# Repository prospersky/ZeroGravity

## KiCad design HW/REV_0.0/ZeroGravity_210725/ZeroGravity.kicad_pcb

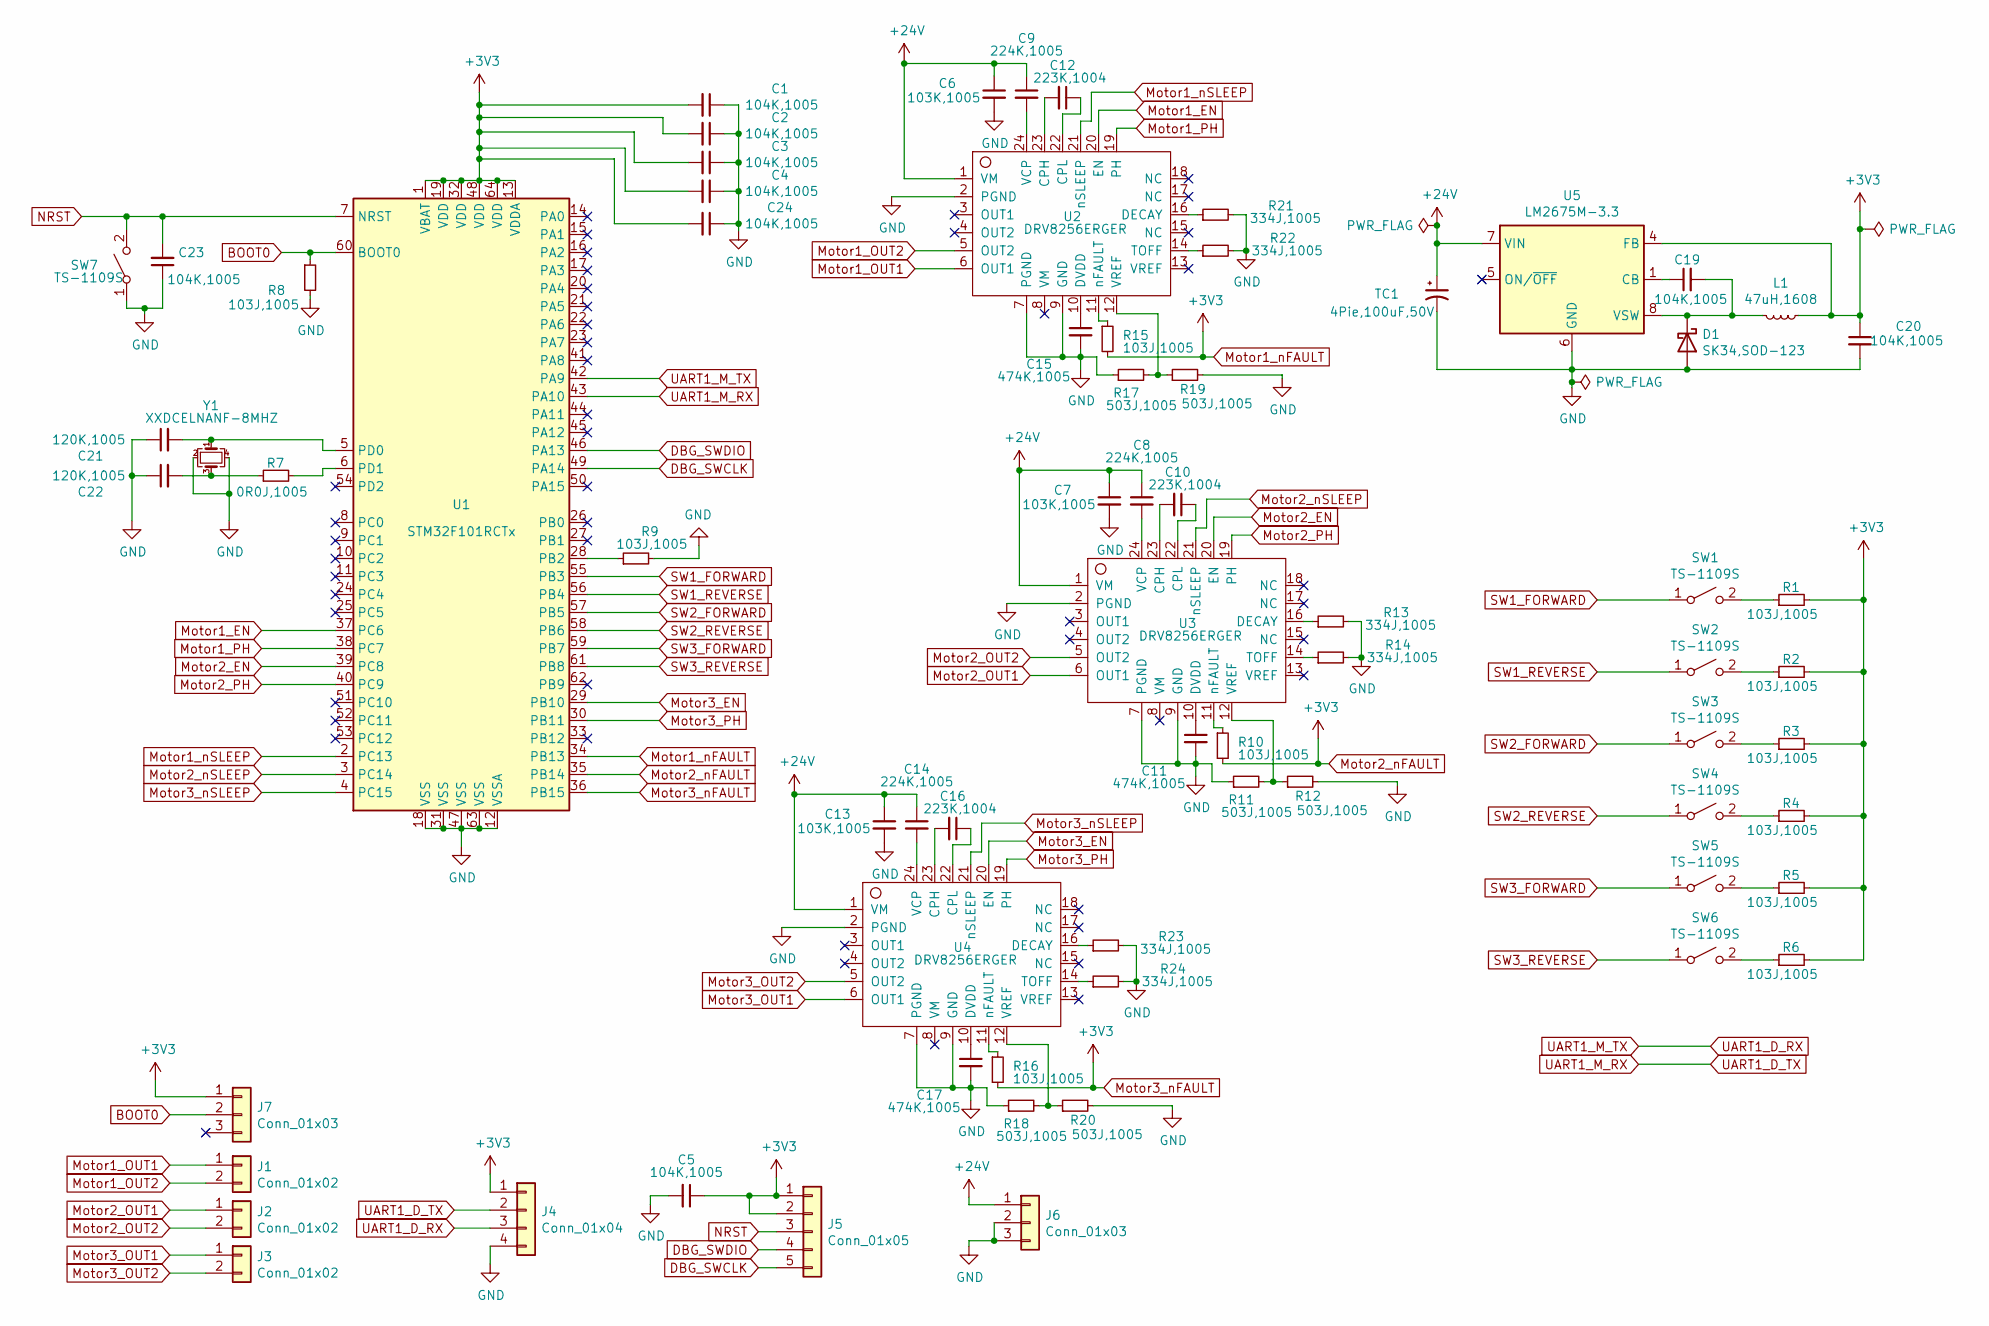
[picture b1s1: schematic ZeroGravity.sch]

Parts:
C1, C2, C3, C4, C5, C19, C20, C23, C24: 104K,1005; C_0402_1005Metric
C6, C7, C13: 103K,1005; C_0402_1005Metric
C8, C9, C14: 224K,1005; C_0402_1005Metric
C10, C12, C16: 223K,1004; C_0402_1005Metric
C11, C15, C17: 474K,1005; C_0402_1005Metric
C21, C22: 120K,1005; C_0402_1005Metric
D1: SK34,SOD-123; D_SOD-123F
J1, J2, J3: Conn_01x02; Molex_PicoBlade_53047-0210_1x02_P1.25mm_Vertical
J4: Conn_01x04; Molex_PicoBlade_53047-0410_1x04_P1.25mm_Vertical
J5: Conn_01x05; Molex_PicoBlade_53047-0510_1x05_P1.25mm_Vertical
J6, J7: Conn_01x03; Molex_PicoBlade_53047-0310_1x03_P1.25mm_Vertical
L1: 47uH,1608; L_0603_1608Metric
R1, R2, R3, R4, R5, R6, R8, R9, R10, R15, R16: 103J,1005; R_0402_1005Metric
R7: 0R0J,1005; R_0402_1005Metric
R11, R12, R17, R18, R19, R20: 503J,1005; R_0402_1005Metric
R13, R14, R21, R22, R23, R24: 334J,1005; R_0402_1005Metric
SW1, SW2, SW3, SW4, SW5, SW6, SW7: TS-1109S; Switch_Tactile_TS-1109S
TC1: 4Pie,100uF,50V; CP_Elec_8x10.5
U1: STM32F101RCTx; LQFP-64_10x10mm_P0.5mm
U2, U3, U4: DRV8256ERGER; VQFN-24-1EP_4x4mm_P0.5mm_EP2.45x2.45mm_ThermalVias
U5: LM2675M-3.3; SOIC-8_3.9x4.9mm_P1.27mm
Y1: XXDCELNANF-8MHZ; Crystal_SMD_7050-4Pin_7.0x5.0mm

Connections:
+24V: C6.1, C7.1, C8.1, C9.1, C13.1, C14.1, J6.1, TC1.1, U2.1 (VM), U3.1 (VM), U4.1 (VM), U5.7 (VIN)
BOOT0: J7.2, R8.1, U1.60 (BOOT0); also elsewhere on the board
DBG_SWCLK: J5.5, U1.49 (PA14)
DBG_SWDIO: J5.4, U1.46 (PA13)
GND: C1.1, C2.1, C3.1, C4.1, C5.2, C6.2, C7.2, C11.2, C13.2, C15.2, C17.2, C20.2, C21.1, C22.1, C23.1, C24.1, D1.2 (A), J4.4, J6.2, J6.3, R8.2, R9.2, R11.1, R12.2, R13.2, R14.2, R17.1, R18.1, R19.2, R20.2, R21.2, R22.2, R23.2, R24.2, SW7.1 (A), TC1.2, U1.12 (VSSA), U1.18 (VSS), U1.31 (VSS), U1.47 (VSS), U1.63 (VSS), U2.2 (PGND), U2.7 (PGND), U2.9 (GND), U3.2 (PGND), U3.7 (PGND), U3.9 (GND), U4.2 (PGND), U4.7 (PGND), U4.9 (GND), U5.6 (GND), Y1.2, Y1.4
Motor1_EN: U1.37 (PC6), U2.20 (EN)
Motor1_OUT1: J1.1, U2.6 (OUT1)
Motor1_OUT2: J1.2, U2.5 (OUT2)
Motor1_PH: U1.38 (PC7), U2.19 (PH)
Motor1_nFAULT: C1.2, C2.2, C3.2, C4.2, C5.1, C20.1, C24.2, J4.1, J5.1, J5.2, J7.1, L1.1, R1.2, R2.2, R3.2, R4.2, R5.2, R6.2, R10.2, R15.2, R16.2, U1.1 (VBAT), U1.13 (VDDA), U1.19 (VDD), U1.32 (VDD), U1.34 (PB13), U1.35 (PB14), U1.36 (PB15), U1.48 (VDD), U1.64 (VDD), U5.4 (FB)
Motor1_nSLEEP: U1.2 (PC13), U2.21 (nSLEEP)
Motor2_EN: U1.39 (PC8), U3.20 (EN)
Motor2_OUT1: J2.1, U3.6 (OUT1)
Motor2_OUT2: J2.2, U3.5 (OUT2)
Motor2_PH: U1.40 (PC9), U3.19 (PH)
Motor2_nSLEEP: U1.3 (PC14), U3.21 (nSLEEP)
Motor3_EN: U1.29 (PB10), U4.20 (EN)
Motor3_OUT1: J3.1, U4.6 (OUT1)
Motor3_OUT2: J3.2, U4.5 (OUT2)
Motor3_PH: U1.30 (PB11), U4.19 (PH)
Motor3_nSLEEP: U1.4 (PC15), U4.21 (nSLEEP)
NRST: C23.2, J5.3, SW7.2 (B), U1.7 (NRST)
unnamed: C8.2, U3.24 (VCP)
unnamed: C9.2, U2.24 (VCP)
unnamed: C10.1, U3.22 (CPL)
unnamed: C10.2, U3.23 (CPH)
unnamed: C11.1, U3.10 (DVDD)
unnamed: C12.1, U2.22 (CPL)
unnamed: C12.2, U2.23 (CPH)
unnamed: C14.2, U4.24 (VCP)
unnamed: C15.1, U2.10 (DVDD)
unnamed: C16.1, U4.22 (CPL)
unnamed: C16.2, U4.23 (CPH)
unnamed: C17.1, U4.10 (DVDD)
unnamed: C19.1, U5.1 (CB)
unnamed 35: C19.2, D1.1 (K), L1.2, U5.8 (VSW); also elsewhere on the board
unnamed: C21.2, U1.5 (PD0), Y1.1
unnamed: C22.2, R7.1, Y1.3
unnamed: R1.1, SW1.2 (B)
unnamed: R2.1, SW2.2 (B)
unnamed: R3.1, SW3.2 (B)
unnamed: R4.1, SW4.2 (B)
unnamed: R5.1, SW5.2 (B)
unnamed: R6.1, SW6.2 (B)
unnamed: R7.2, U1.6 (PD1)
unnamed: R9.1, U1.28 (PB2)
unnamed: R10.1, U3.11 (nFAULT)
unnamed: R11.2, R12.1, U3.12 (VREF)
unnamed: R13.1, U3.16 (DECAY)
unnamed: R14.1, U3.14 (TOFF)
unnamed: R15.1, U2.11 (nFAULT)
unnamed: R16.1, U4.11 (nFAULT)
unnamed: R17.2, R19.1, U2.12 (VREF)
unnamed: R18.2, R20.1, U4.12 (VREF)
unnamed: R21.1, U2.16 (DECAY)
unnamed: R22.1, U2.14 (TOFF)
unnamed: R23.1, U4.16 (DECAY)
unnamed: R24.1, U4.14 (TOFF)
SW1_FORWARD: SW1.1 (A), U1.55 (PB3)
SW1_REVERSE: SW2.1 (A), U1.56 (PB4)
SW2_FORWARD: SW3.1 (A), U1.57 (PB5)
SW2_REVERSE: SW4.1 (A), U1.58 (PB6)
SW3_FORWARD: SW5.1 (A), U1.59 (PB7)
SW3_REVERSE: SW6.1 (A), U1.61 (PB8)
UART1_D_RX: J4.3, U1.42 (PA9)
UART1_D_TX: J4.2, U1.43 (PA10)

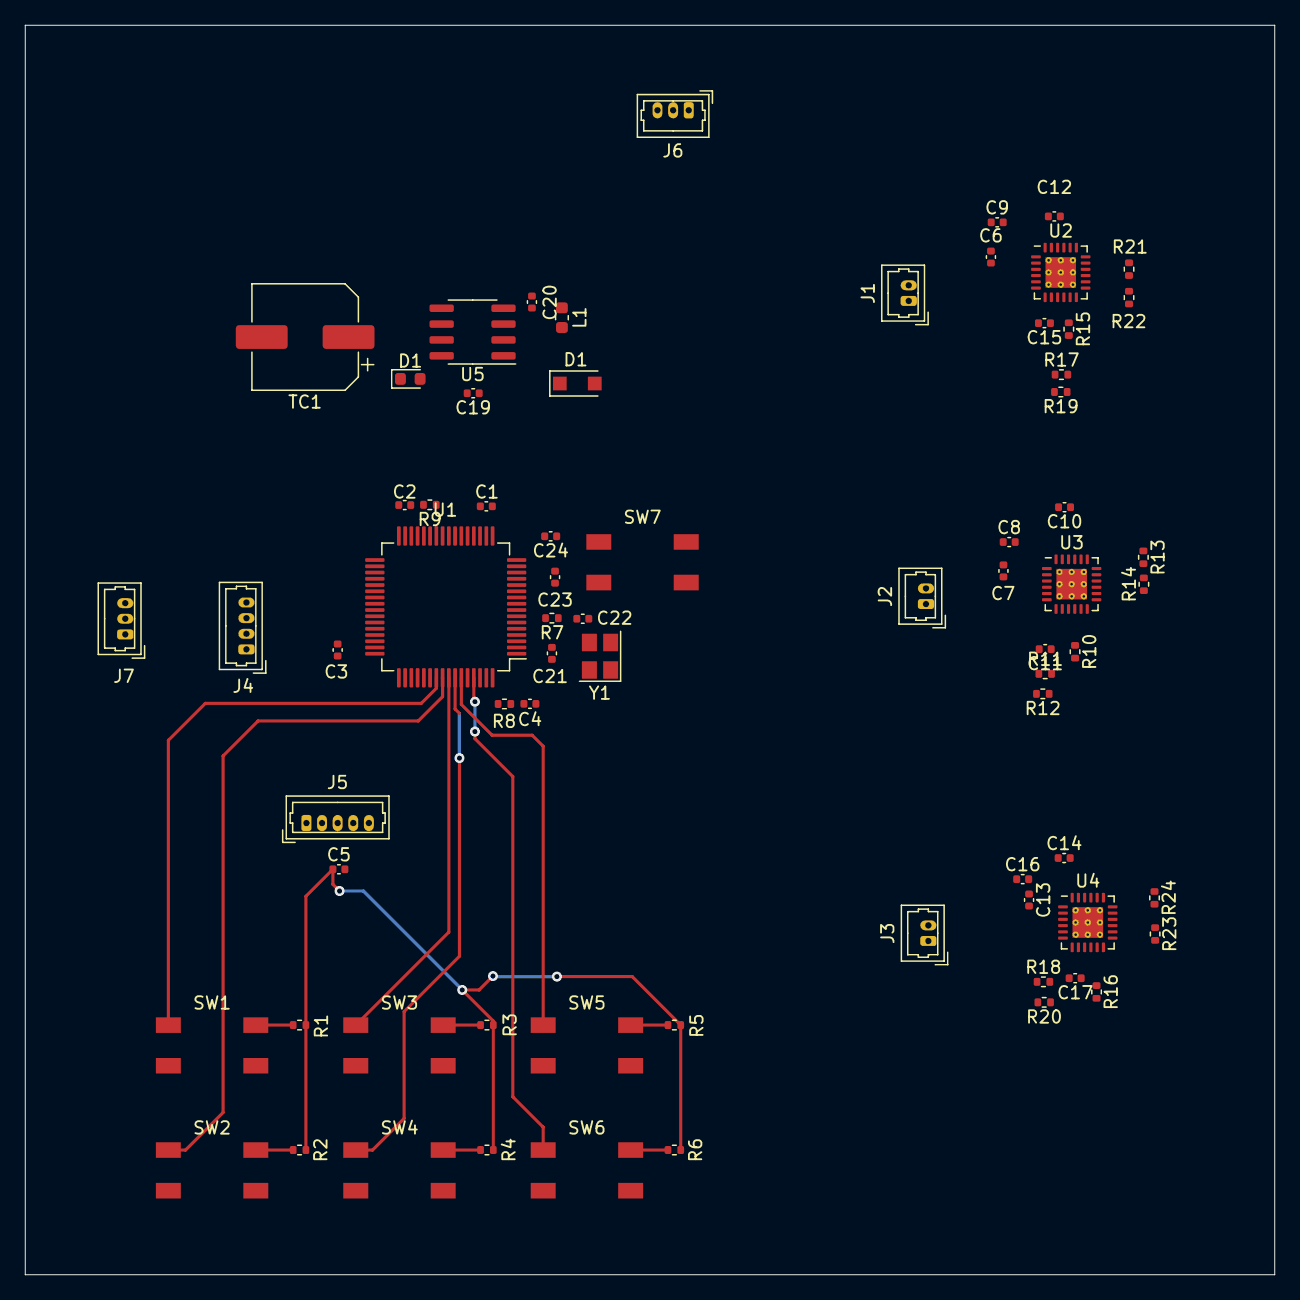
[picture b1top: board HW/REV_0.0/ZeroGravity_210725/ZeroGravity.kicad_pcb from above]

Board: 2 copper layers, 100.0 x 100.0 mm, 71 parts (0 on the bottom side), 66 nets.

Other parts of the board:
D1#2: DIODE; D_0603_1608Metric

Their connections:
BOOT0: D1#2.1; also elsewhere on the board
unnamed 35: D1#2.2; also elsewhere on the board

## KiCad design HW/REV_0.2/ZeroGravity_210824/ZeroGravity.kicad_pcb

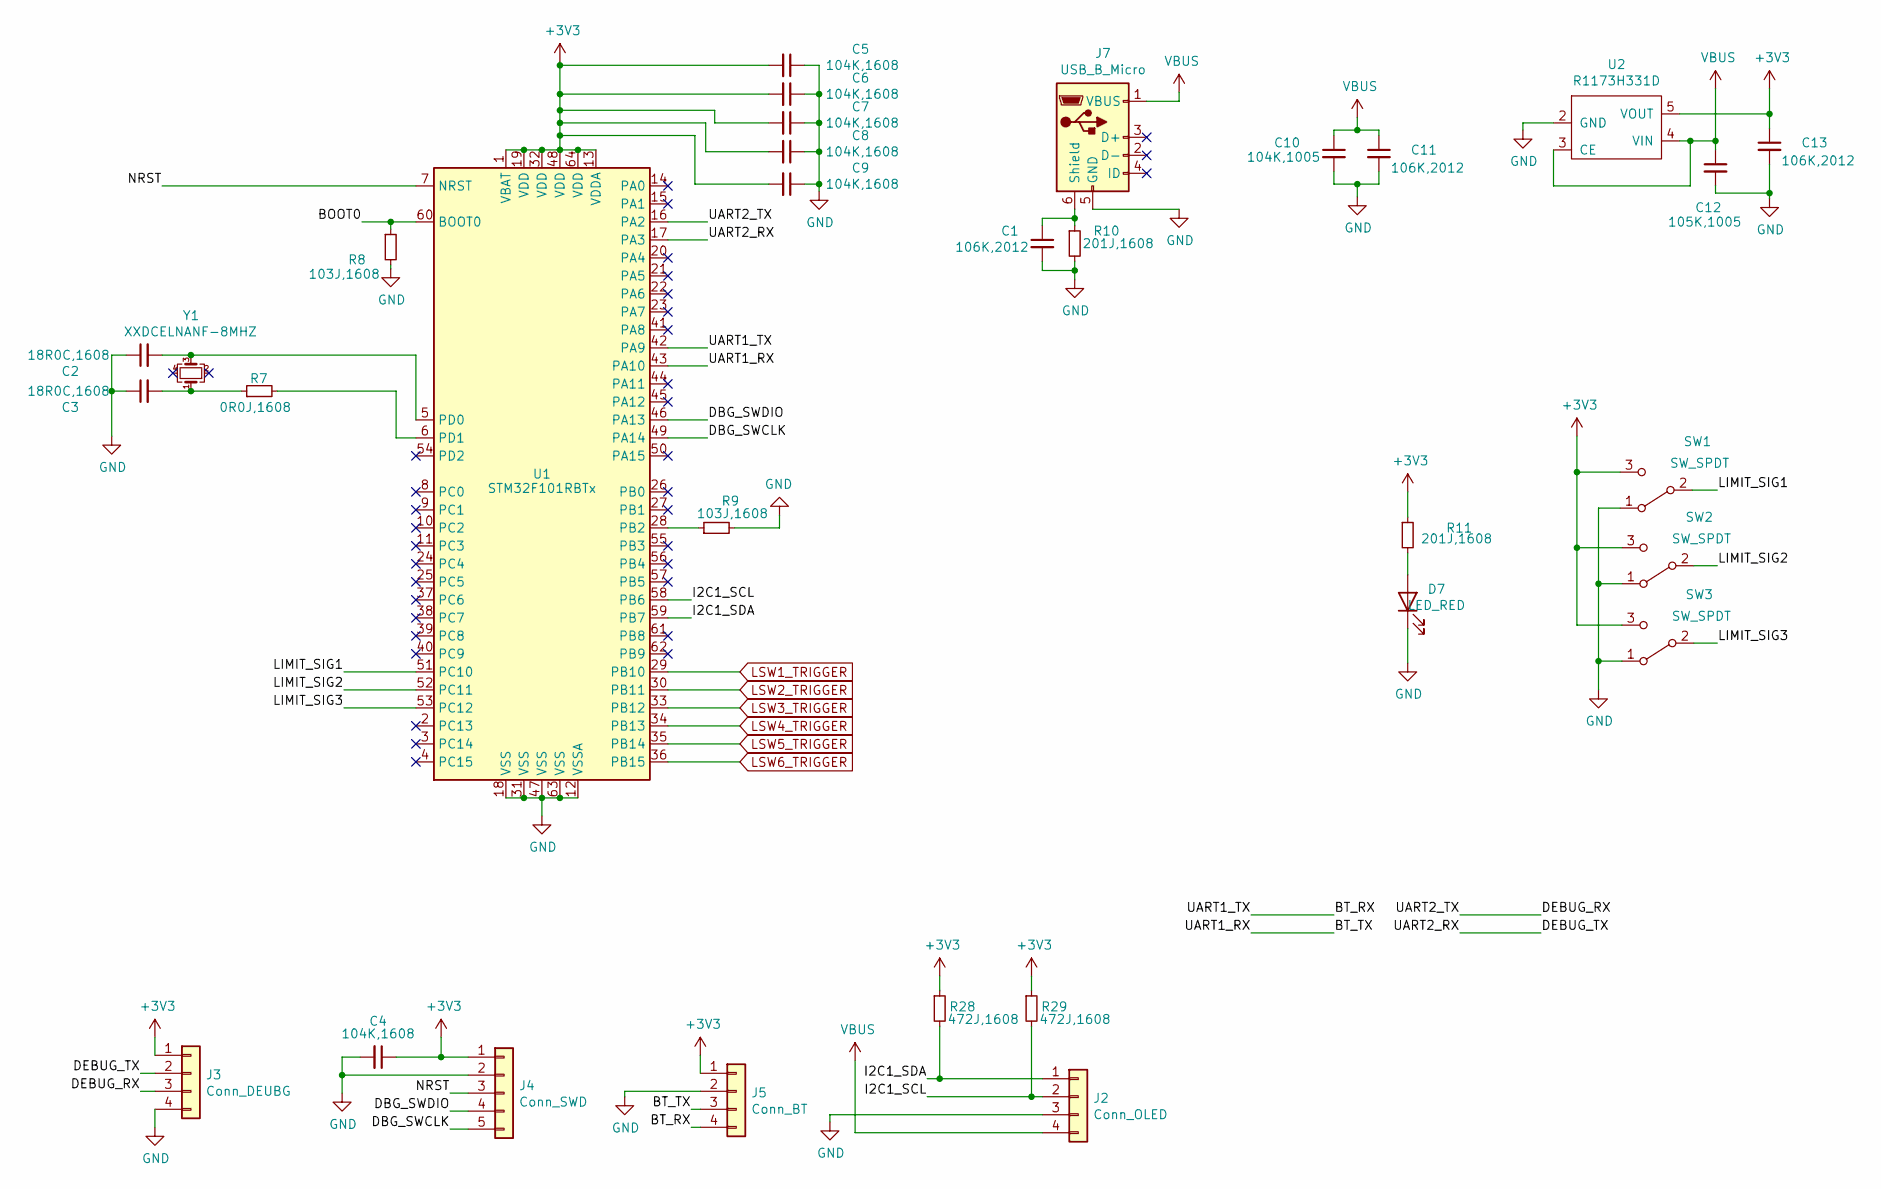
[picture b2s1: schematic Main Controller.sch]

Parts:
C1, C11, C13: 106K,2012; C_0805_2012Metric
C2, C3: 18R0C,1608; C_0603_1608Metric_Pad1.08x0.95mm_HandSolder
C4, C5, C6, C7, C8, C9: 104K,1608; C_0603_1608Metric_Pad1.08x0.95mm_HandSolder
C10: 104K,1005; C_0603_1608Metric_Pad1.08x0.95mm_HandSolder
C12: 105K,1005; C_0603_1608Metric_Pad1.08x0.95mm_HandSolder
D7: LED_RED; LED_0603_1608Metric
J2: Conn_OLED; PinSocket_1x04_P2.54mm_Vertical
J3: Conn_DEUBG; PinSocket_1x04_P2.54mm_Vertical
J4: Conn_SWD; PinSocket_1x05_P2.54mm_Vertical
J5: Conn_BT; PinHeader_1x04_P2.54mm_Vertical
J7: USB_B_Micro; USB_Micro-B_Molex-105017-0001
R7: 0R0J,1608; R_0603_1608Metric_Pad0.98x0.95mm_HandSolder
R8, R9: 103J,1608; R_0603_1608Metric_Pad0.98x0.95mm_HandSolder
R10, R11: 201J,1608; R_0603_1608Metric_Pad0.98x0.95mm_HandSolder
R28, R29: 472J,1608; R_0603_1608Metric_Pad0.98x0.95mm_HandSolder
SW1, SW2, SW3: SW_SPDT; DB2C-C1AA
U1: STM32F101RBTx; LQFP-64_10x10mm_P0.5mm
U2: R1173H331D; SOT-89-5
Y1: XXDCELNANF-8MHZ; Crystal_SMD_7050-4Pin_7.0x5.0mm

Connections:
+3V3: C4.1, C5.2, C6.2, C7.2, C8.2, C9.2, C13.1, J3.1, J4.1, J5.1, R11.1, R28.1, R29.1, SW1.3 (C), SW2.3 (C), SW3.3 (C), U1.1 (VBAT), U1.13 (VDDA), U1.19 (VDD), U1.32 (VDD), U1.48 (VDD), U1.64 (VDD), U2.5 (VOUT)
/Main Controller/BOOT0: R8.1, U1.60 (BOOT0)
/Main Controller/BT_RX: J5.4, U1.42 (PA9)
/Main Controller/BT_TX: J5.3, U1.43 (PA10)
/Main Controller/DBG_SWCLK: J4.5, U1.49 (PA14)
/Main Controller/DBG_SWDIO: J4.4, U1.46 (PA13)
/Main Controller/DEBUG_RX: J3.3, U1.16 (PA2)
/Main Controller/DEBUG_TX: J3.2, U1.17 (PA3)
/Main Controller/I2C1_SCL: J2.2, R29.2, U1.58 (PB6)
/Main Controller/I2C1_SDA: J2.1, R28.2, U1.59 (PB7)
/Main Controller/LIMIT_SIG1: SW1.2 (B), U1.51 (PC10)
/Main Controller/LIMIT_SIG2: SW2.2 (B), U1.52 (PC11)
/Main Controller/LIMIT_SIG3: SW3.2 (B), U1.53 (PC12)
/Main Controller/NRST: J4.3, U1.7 (NRST)
GND: C1.2, C2.1, C3.1, C4.2, C5.1, C6.1, C7.1, C8.1, C9.1, C10.2, C11.2, C12.2, C13.2, D7.1 (K), J2.3, J3.4, J4.2, J5.2, J7.5 (GND), R8.2, R9.2, R10.2, SW1.1 (A), SW2.1 (A), SW3.1 (A), U1.12 (VSSA), U1.18 (VSS), U1.31 (VSS), U1.47 (VSS), U1.63 (VSS), U2.2 (GND); also elsewhere on the board
LSW1_TRIGGER: U1.29 (PB10); also elsewhere on the board
LSW2_TRIGGER: U1.30 (PB11); also elsewhere on the board
LSW3_TRIGGER: U1.33 (PB12); also elsewhere on the board
LSW4_TRIGGER: U1.34 (PB13); also elsewhere on the board
LSW5_TRIGGER: U1.35 (PB14); also elsewhere on the board
LSW6_TRIGGER: U1.36 (PB15); also elsewhere on the board
unnamed: C1.1, J7.6 (Shield), R10.1
unnamed: C2.2, U1.5 (PD0), Y1.3
unnamed: C3.2, R7.1, Y1.1
unnamed: D7.2 (A), R11.2
unnamed: R7.2, U1.6 (PD1)
unnamed: R9.1, U1.28 (PB2)
VBUS: C10.1, C11.1, C12.1, J2.4, J7.1 (VBUS), U2.3 (CE), U2.4 (VIN); also elsewhere on the board

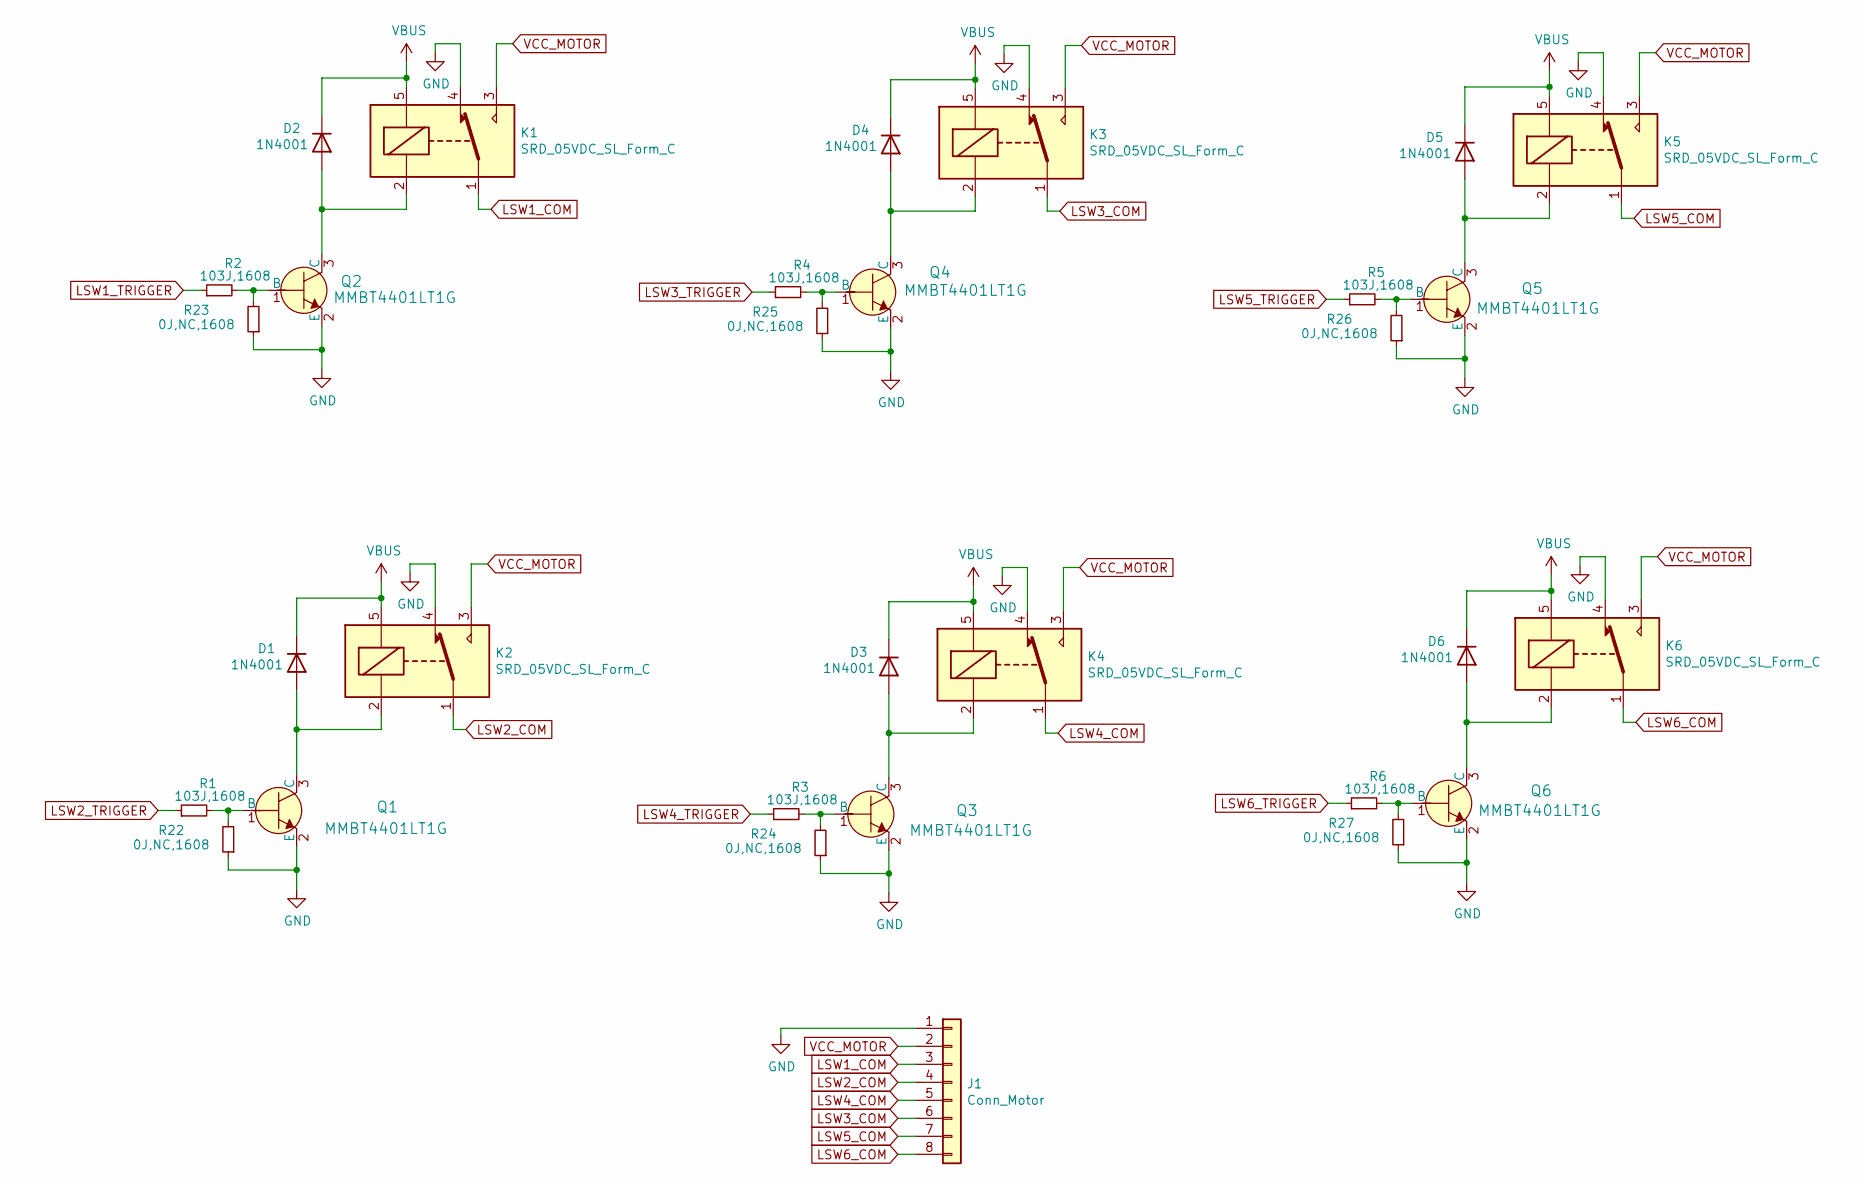
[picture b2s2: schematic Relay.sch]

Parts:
D1, D2, D3, D4, D5, D6: 1N4001; D_DO-41_SOD81_P10.16mm_Horizontal
J1: Conn_Motor; PinHeader_1x08_P2.54mm_Vertical
K1, K2, K3, K4, K5, K6: SRD_05VDC_SL_Form_C; Relay_SPDT_SANYOU_SRD_Series_Form_C
Q1, Q2, Q3, Q4, Q5, Q6: MMBT4401LT1G; SOT-23-3; MPN MMBT4401LT1G; Digi-Key_PN MMBT4401LT1GOSCT-ND
R1, R2, R3, R4, R5, R6: 103J,1608; R_0603_1608Metric_Pad0.98x0.95mm_HandSolder
R22, R23, R24, R25, R26, R27: 0J,NC,1608; R_0603_1608Metric_Pad0.98x0.95mm_HandSolder

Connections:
GND: J1.1, K1.4, K2.4, K3.4, K4.4, K5.4, K6.4, Q1.2 (E), Q2.2 (E), Q3.2 (E), Q4.2 (E), Q5.2 (E), Q6.2 (E), R22.1, R23.1, R24.1, R25.1, R26.1, R27.1; also elsewhere on the board
LSW1_COM: J1.3, K1.1
LSW1_TRIGGER: R2.1; also elsewhere on the board
LSW2_COM: J1.4, K2.1
LSW2_TRIGGER: R1.1; also elsewhere on the board
LSW3_COM: J1.6, K3.1
LSW3_TRIGGER: R4.1; also elsewhere on the board
LSW4_COM: J1.5, K4.1
LSW4_TRIGGER: R3.1; also elsewhere on the board
LSW5_COM: J1.7, K5.1
LSW5_TRIGGER: R5.1; also elsewhere on the board
LSW6_COM: J1.8, K6.1
LSW6_TRIGGER: R6.1; also elsewhere on the board
unnamed: D1.2 (A), K2.2, Q1.3 (C)
unnamed: D2.2 (A), K1.2, Q2.3 (C)
unnamed: D3.2 (A), K4.2, Q3.3 (C)
unnamed: D4.2 (A), K3.2, Q4.3 (C)
unnamed: D5.2 (A), K5.2, Q5.3 (C)
unnamed: D6.2 (A), K6.2, Q6.3 (C)
unnamed: Q1.1 (B), R1.2, R22.2
unnamed: Q2.1 (B), R2.2, R23.2
unnamed: Q3.1 (B), R3.2, R24.2
unnamed: Q4.1 (B), R4.2, R25.2
unnamed: Q5.1 (B), R5.2, R26.2
unnamed: Q6.1 (B), R6.2, R27.2
VBUS: D1.1 (K), D2.1 (K), D3.1 (K), D4.1 (K), D5.1 (K), D6.1 (K), K1.5, K2.5, K3.5, K4.5, K5.5, K6.5; also elsewhere on the board
VCC_MOTOR: J1.2, K1.3, K2.3, K3.3, K4.3, K5.3, K6.3

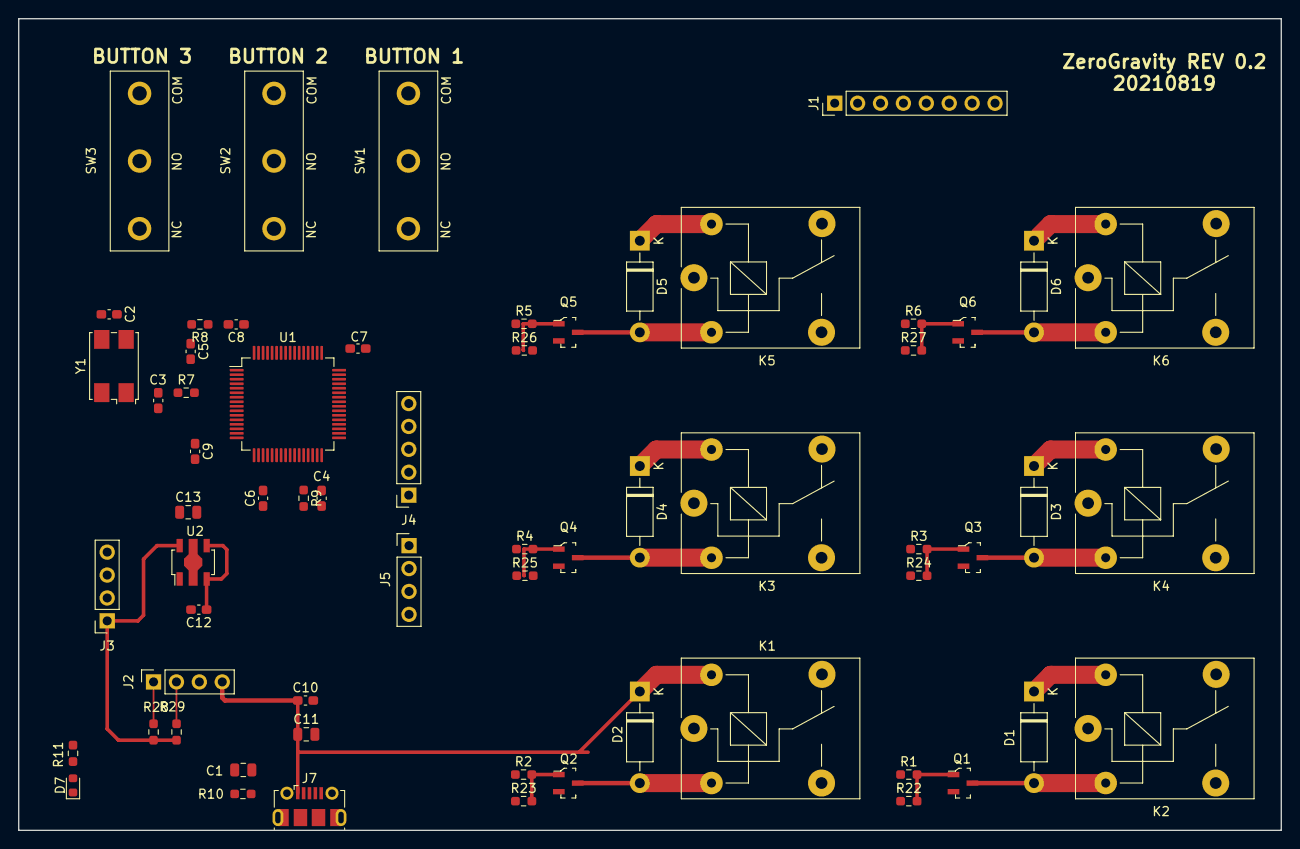
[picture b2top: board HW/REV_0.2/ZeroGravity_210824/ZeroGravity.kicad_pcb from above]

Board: 2 copper layers, 140.0 x 90.0 mm, 63 parts (0 on the bottom side), 47 nets.

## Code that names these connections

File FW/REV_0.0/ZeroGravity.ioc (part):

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PD1-OSC_OUT.Mode=HSE-External-Oscillator
PA10.Mode=Asynchronous
Mcu.UserName=STM32F101RCTx
PC10.Signal=GPIO_Input
PC11.Signal=GPIO_Input
PC12.Signal=GPIO_Input
PC13-TAMPER-RTC.Signal=GPIO_Input
PD0-OSC_IN.Signal=RCC_OSC_IN
PC14-OSC32_IN.Signal=GPIO_Input
PB11.Signal=GPIO_Output
PB15.Signal=GPIO_Output
PB13.Signal=GPIO_Output
PD1-OSC_OUT.Signal=RCC_OSC_OUT
PA13.Signal=SYS_JTMS-SWDIO
PA3.Mode=Asynchronous
PA9.Mode=Asynchronous
PA9.Signal=USART1_TX
PB6.Signal=I2C1_SCL
PB6.Mode=I2C
PC15-OSC32_OUT.Signal=GPIO_Input
PB10.Signal=GPIO_Output
PD0-OSC_IN.Mode=HSE-External-Oscillator
PB14.Signal=GPIO_Output
board=custom
PA14.Mode=Serial_Wire
PB7.Signal=I2C1_SDA
PA13.Mode=Serial_Wire
Mcu.Name=STM32F101R(C-D-E)Tx
PA2.Signal=USART2_TX
Mcu.Package=LQFP64
PB7.Mode=I2C
PA10.Signal=USART1_RX
PA14.Signal=SYS_JTCK-SWCLK
PA2.Mode=Asynchronous
PB12.Signal=GPIO_Output
PA3.Signal=USART2_RX

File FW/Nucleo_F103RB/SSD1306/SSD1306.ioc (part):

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Mcu.UserName=STM32F103RBTx
PB10.Mode=Asynchronous
PC13-TAMPER-RTC.GPIOParameters=GPIO_PuPd,GPIO_Label
PA14.GPIO_Label=TCK
PB11.Signal=USART3_RX
RCC.SYSCLKSource=RCC_SYSCLKSOURCE_PLLCLK
PD1-OSC_OUT.Signal=RCC_OSC_OUT
PC14-OSC32_IN.Mode=LSE-External-Oscillator
PA14.Mode=Serial_Wire
PA5.GPIO_PuPd=GPIO_NOPULL
PB3.GPIOParameters=GPIO_Label
PA13.GPIOParameters=GPIO_Label
PB9.Signal=I2C1_SDA
Mcu.Package=LQFP64
PC13-TAMPER-RTC.GPIO_PuPd=GPIO_NOPULL
PA10.Signal=USART1_RX
PA5.GPIOParameters=GPIO_Speed,GPIO_PuPd,GPIO_Label,GPIO_ModeDefaultOutputPP
PB3.GPIO_Label=SWO
PC15-OSC32_OUT.Mode=LSE-External-Oscillator
PD1-OSC_OUT.Mode=HSE-External-Clock-Source
PA10.Mode=Asynchronous
PC13-TAMPER-RTC.Signal=GPXTI13
PD0-OSC_IN.Signal=RCC_OSC_IN
PC14-OSC32_IN.Signal=RCC_OSC32_IN
boardIOC=true
PA13.Signal=SYS_JTMS-SWDIO
PA9.Mode=Asynchronous
PB11.Mode=Asynchronous
PB9.Mode=I2C
PA9.Signal=USART1_TX
PC15-OSC32_OUT.Signal=RCC_OSC32_OUT
PD0-OSC_IN.Mode=HSE-External-Clock-Source
PB10.Signal=USART3_TX
PA5.Signal=GPIO_Output
board=NUCLEO-F103RB
PC13-TAMPER-RTC.GPIO_Label=B1 [Blue PushButton]
PA5.GPIO_ModeDefaultOutputPP=GPIO_MODE_OUTPUT_PP
PA13.Mode=Serial_Wire
Mcu.Name=STM32F103R(8-B)Tx
PA13.GPIO_Label=TMS
PB3.Signal=SYS_JTDO-TRACESWO
RCC.SYSCLKFreq_VALUE=64000000
PA5.GPIO_Label=LD2 [Green Led]
PA14.GPIOParameters=GPIO_Label
PA14.Signal=SYS_JTCK-SWCLK
PA5.GPIO_Speed=GPIO_SPEED_FREQ_LOW
PB8.Mode=I2C
PB8.Signal=I2C1_SCL
